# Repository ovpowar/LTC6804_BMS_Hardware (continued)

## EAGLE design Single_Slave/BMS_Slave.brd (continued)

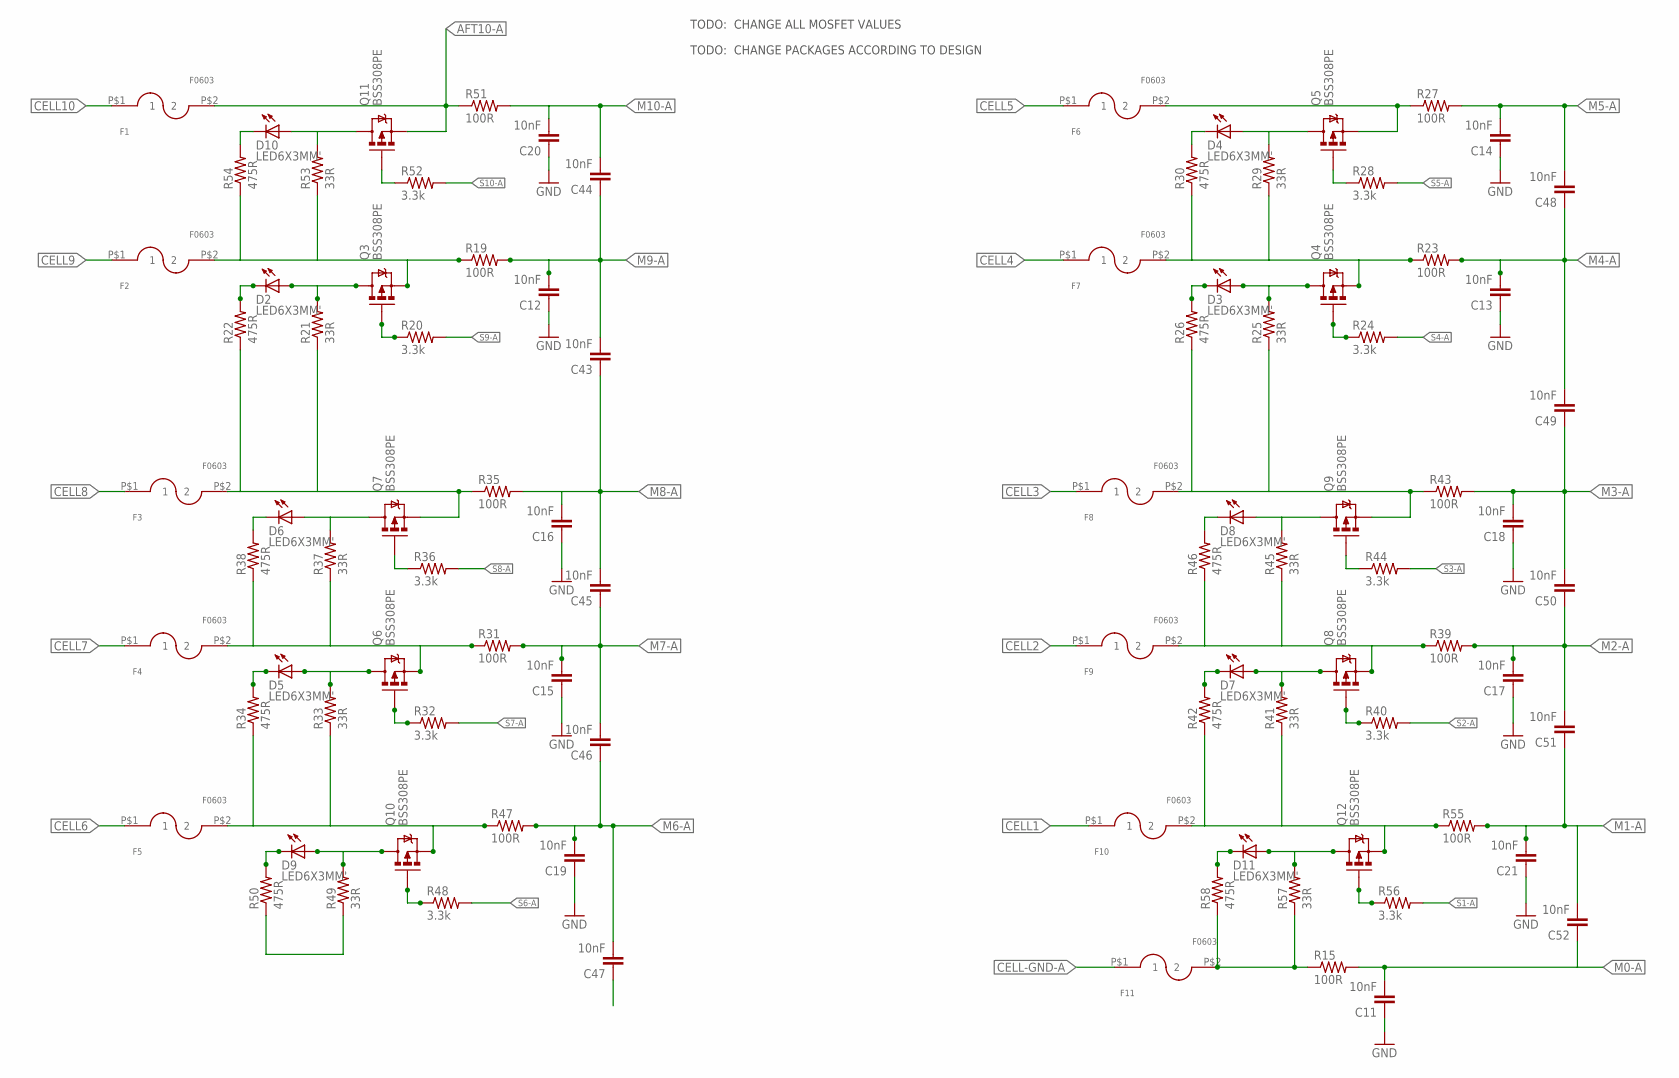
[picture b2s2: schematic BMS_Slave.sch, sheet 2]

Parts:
C11, C12, C13, C14, C15, C16, C17, C18, C19, C20, C21, C43, C44, C45, C46, C47, C48, C49, C50, C51, C52: 10nF; 0603
D2, D3, D4, D5, D6, D7, D8, D9, D10, D11: LED6X3MM'; LED0603
F1, F2, F3, F4, F5, F6, F7, F8, F9, F10, F11: F0603; 0603
Q3, Q4, Q5, Q6, Q7, Q8, Q9, Q10, Q11, Q12: BSS308PE; SOT23-3
R15, R19, R23, R27, R31, R35, R39, R43, R47, R51, R55: 100R; 0603
R20, R24, R28, R32, R36, R40, R44, R48, R52, R56: 3.3k; 0603
R21, R25, R29, R33, R37, R41, R45, R49, R53, R57: 33R; 2512
R22, R26, R30, R34, R38, R42, R46, R50, R54, R58: 475R; 0603

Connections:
AFT0: F11.P$2 (2), R15.P$1 (1), R57.1, R58.P$1 (1)
AFT1: F10.P$2 (2), Q12.2 (S), R41.1, R42.P$1 (1), R55.P$1 (1)
AFT2: F9.P$2 (2), Q8.2 (S), R39.P$1 (1), R45.1, R46.P$1 (1)
AFT3: F8.P$2 (2), Q9.2 (S), R25.1, R26.P$1 (1), R43.P$1 (1)
AFT4: F7.P$2 (2), Q4.2 (S), R23.P$1 (1), R29.1, R30.P$1 (1)
AFT5: F6.P$2 (2), Q5.2 (S), R27.P$1 (1), R49.1, R50.P$1 (1)
AFT6: F5.P$2 (2), Q10.2 (S), R33.1, R34.P$1 (1), R47.P$1 (1)
AFT7: F4.P$2 (2), Q6.2 (S), R31.P$1 (1), R37.1, R38.P$1 (1)
AFT8: F3.P$2 (2), Q7.2 (S), R21.1, R22.P$1 (1), R35.P$1 (1)
AFT9: F2.P$2 (2), Q3.2 (S), R19.P$1 (1), R53.1, R54.P$1 (1)
AFT10-A: F1.P$2 (2), Q11.2 (S), R51.P$1 (1); also elsewhere on the board
CELL1: F10.P$1 (1); also elsewhere on the board
CELL2: F9.P$1 (1); also elsewhere on the board
CELL3: F8.P$1 (1); also elsewhere on the board
CELL4: F7.P$1 (1); also elsewhere on the board
CELL5: F6.P$1 (1); also elsewhere on the board
CELL6: F5.P$1 (1); also elsewhere on the board
CELL7: F4.P$1 (1); also elsewhere on the board
CELL8: F3.P$1 (1); also elsewhere on the board
CELL9: F2.P$1 (1); also elsewhere on the board
CELL10: F1.P$1 (1); also elsewhere on the board
CELL-GND-A: F11.P$1 (1); also elsewhere on the board
GNDA: C11.P$1 (1), C12.P$1 (1), C13.P$1 (1), C14.P$1 (1), C15.P$1 (1), C16.P$1 (1), C17.P$1 (1), C18.P$1 (1), C19.P$1 (1), C20.P$1 (1), C21.P$1 (1); also elsewhere on the board
M0-A: C11.P$2 (2), C52.P$1 (1), R15.P$2 (2); also elsewhere on the board
M1-A: C21.P$2 (2), C51.P$1 (1), C52.P$2 (2), R55.P$2 (2); also elsewhere on the board
M2-A: C17.P$2 (2), C50.P$1 (1), C51.P$2 (2), R39.P$2 (2); also elsewhere on the board
M3-A: C18.P$2 (2), C49.P$1 (1), C50.P$2 (2), R43.P$2 (2); also elsewhere on the board
M4-A: C13.P$2 (2), C48.P$1 (1), C49.P$2 (2), R23.P$2 (2); also elsewhere on the board
M5-A: C14.P$2 (2), C47.P$1 (1), C48.P$2 (2), R27.P$2 (2); also elsewhere on the board
M6-A: C19.P$2 (2), C46.P$1 (1), C47.P$2 (2), R47.P$2 (2); also elsewhere on the board
M7-A: C15.P$2 (2), C45.P$1 (1), C46.P$2 (2), R31.P$2 (2); also elsewhere on the board
M8-A: C16.P$2 (2), C43.P$1 (1), C45.P$2 (2), R35.P$2 (2); also elsewhere on the board
M9-A: C12.P$2 (2), C43.P$2 (2), C44.P$1 (1), R19.P$2 (2); also elsewhere on the board
M10-A: C20.P$2 (2), C44.P$2 (2), R51.P$2 (2); also elsewhere on the board
unnamed: D2.P$1 (A), Q3.3 (D), R21.2
unnamed: D2.P$2 (C), R22.P$2 (2)
unnamed: Q3.1 (G), R20.P$1 (1)
unnamed: D3.P$1 (A), Q4.3 (D), R25.2
unnamed: D3.P$2 (C), R26.P$2 (2)
unnamed: Q4.1 (G), R24.P$1 (1)
unnamed: D4.P$1 (A), Q5.3 (D), R29.2
unnamed: D4.P$2 (C), R30.P$2 (2)
unnamed: Q5.1 (G), R28.P$1 (1)
unnamed: D5.P$1 (A), Q6.3 (D), R33.2
unnamed: D5.P$2 (C), R34.P$2 (2)
unnamed: Q6.1 (G), R32.P$1 (1)
unnamed: D6.P$1 (A), Q7.3 (D), R37.2
unnamed: D6.P$2 (C), R38.P$2 (2)
unnamed: Q7.1 (G), R36.P$1 (1)
unnamed: D7.P$1 (A), Q8.3 (D), R41.2
unnamed: D7.P$2 (C), R42.P$2 (2)
unnamed: Q8.1 (G), R40.P$1 (1)
unnamed: D8.P$1 (A), Q9.3 (D), R45.2
unnamed: D8.P$2 (C), R46.P$2 (2)
unnamed: Q9.1 (G), R44.P$1 (1)
unnamed: D10.P$1 (A), Q11.3 (D), R53.2
unnamed: D10.P$2 (C), R54.P$2 (2)
unnamed: Q11.1 (G), R52.P$1 (1)
unnamed: D9.P$1 (A), Q10.3 (D), R49.2
unnamed: D9.P$2 (C), R50.P$2 (2)
unnamed: Q10.1 (G), R48.P$1 (1)
unnamed: D11.P$1 (A), Q12.3 (D), R57.2
unnamed: D11.P$2 (C), R58.P$2 (2)
unnamed: Q12.1 (G), R56.P$1 (1)
S1-A: R56.P$2 (2); also elsewhere on the board
S2-A: R40.P$2 (2); also elsewhere on the board
S3-A: R44.P$2 (2); also elsewhere on the board
S4-A: R24.P$2 (2); also elsewhere on the board
S5-A: R28.P$2 (2); also elsewhere on the board
S6-A: R48.P$2 (2); also elsewhere on the board
S7-A: R32.P$2 (2); also elsewhere on the board
S8-A: R36.P$2 (2); also elsewhere on the board
S9-A: R20.P$2 (2); also elsewhere on the board
S10-A: R52.P$2 (2); also elsewhere on the board

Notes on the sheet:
TODO: CHANGE ALL MOSFET VALUES
TODO: CHANGE PACKAGES ACCORDING TO DESIGN

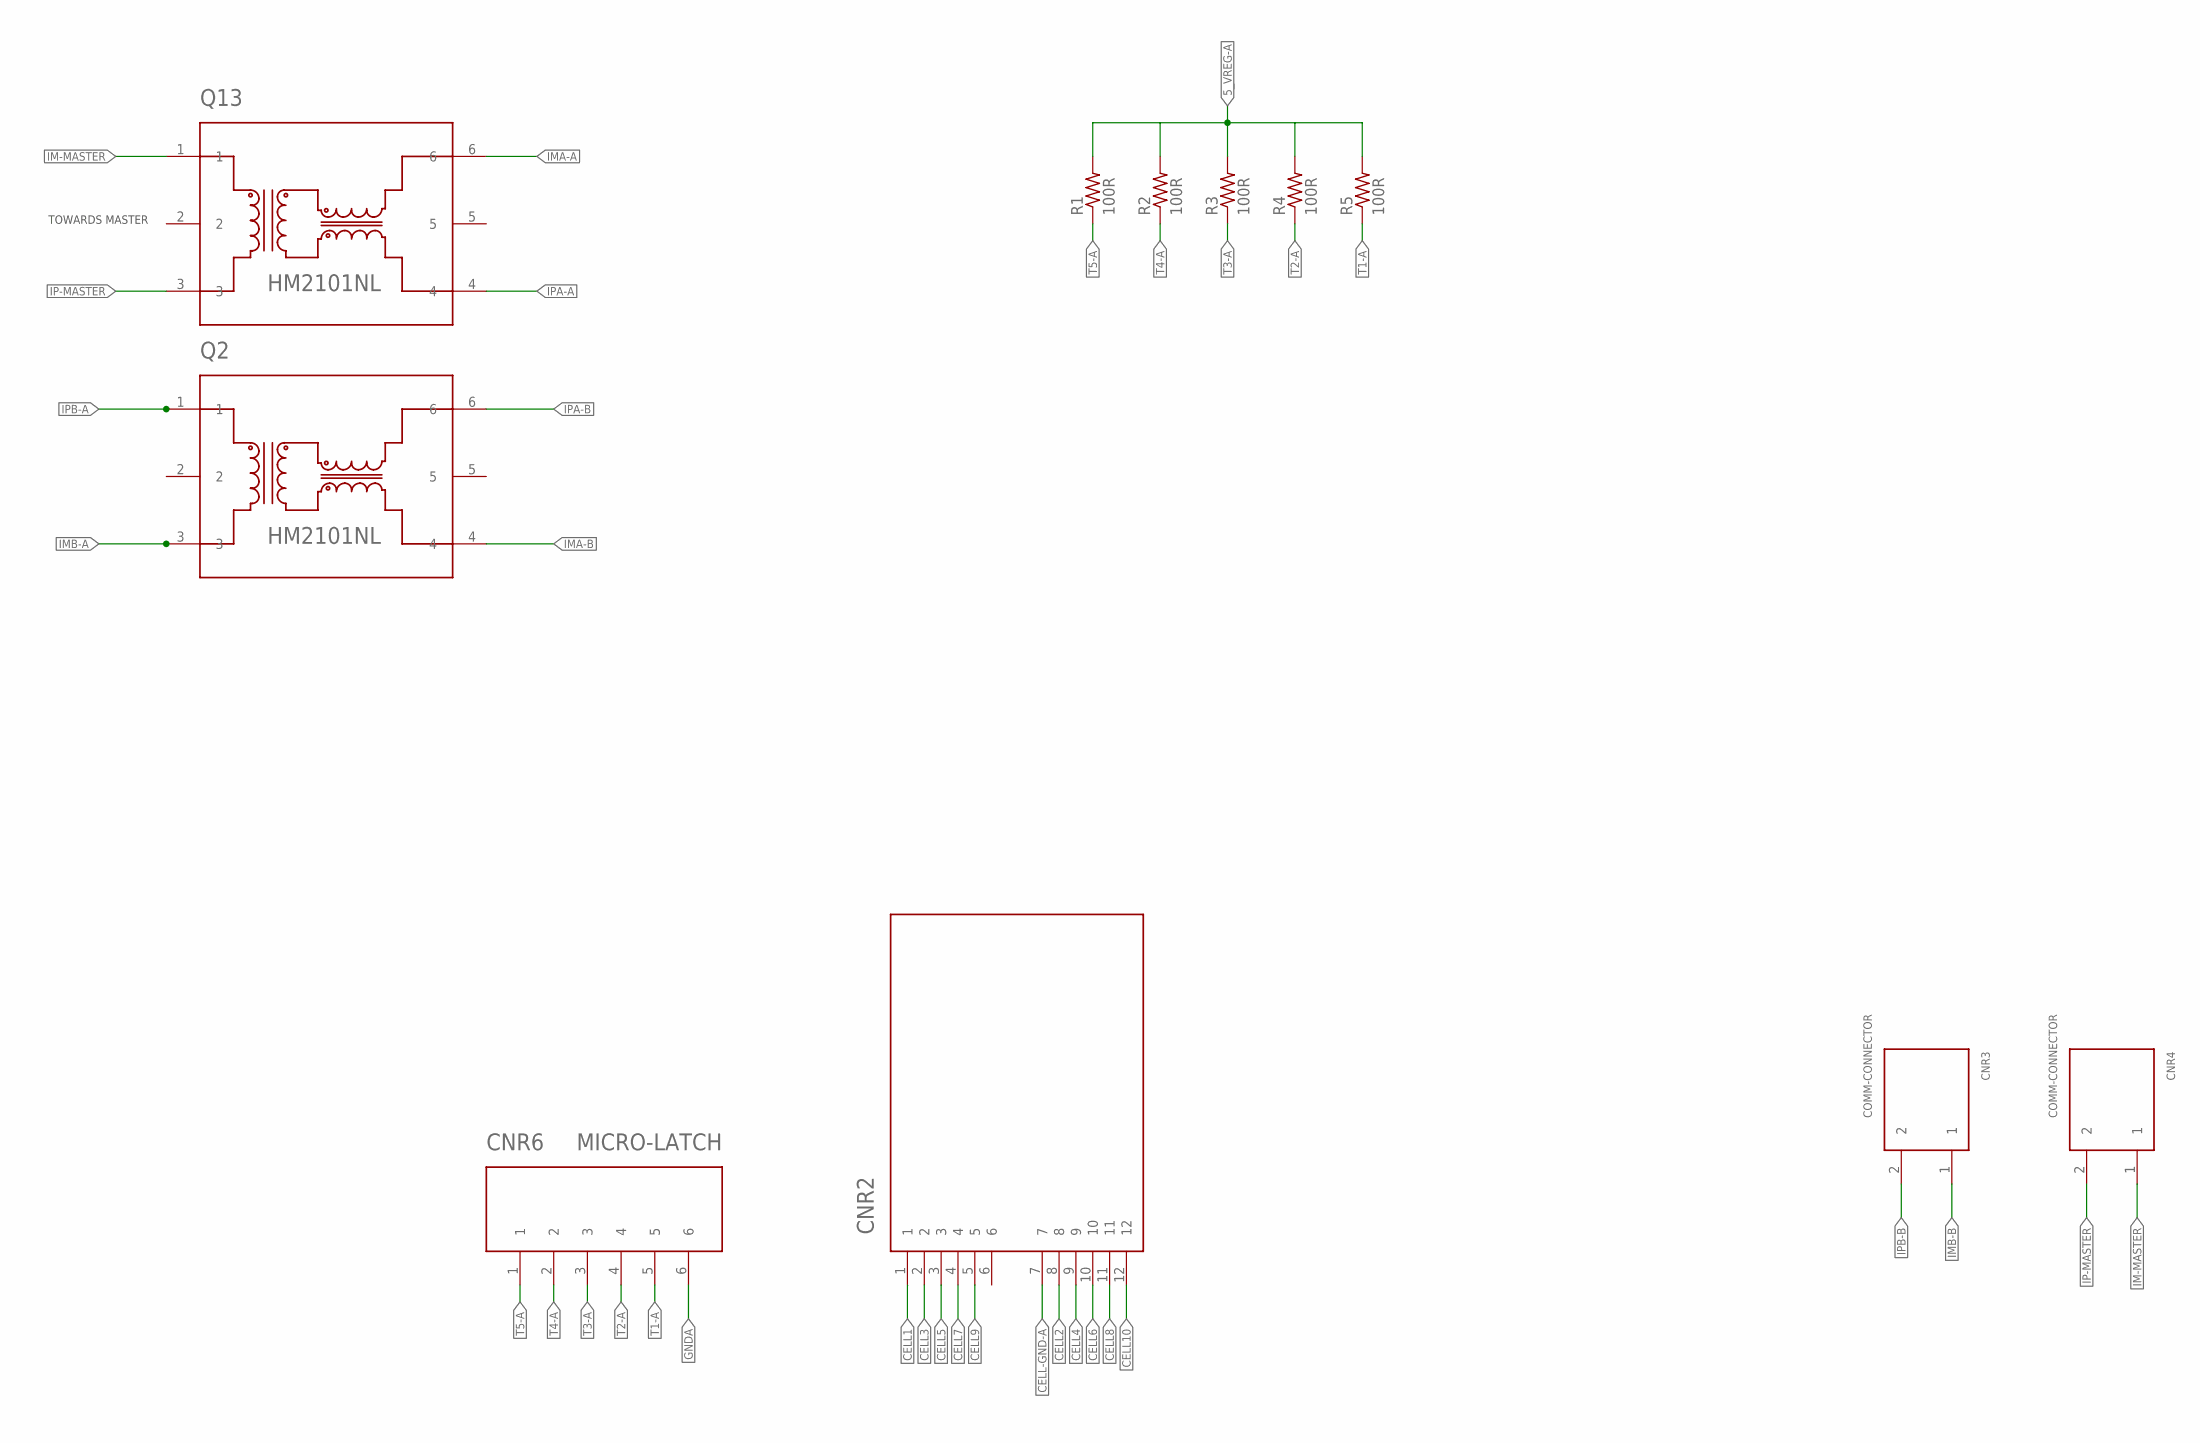
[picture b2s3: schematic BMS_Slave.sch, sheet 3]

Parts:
CNR2: CELL-CONNECTORMOLEX-MICROFIT; 0430451200
CNR3, CNR4: COMM-CONNECTOR; 105313-2202
CNR6: MICRO-LATCH; 0532530670
Q2, Q13: HM2101NL
R1, R2, R3, R4, R5: 100R; 0603

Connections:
5_VREG-A: R1.P$2 (2), R2.P$2 (2), R3.P$2 (2), R4.P$2 (2), R5.P$2 (2); also elsewhere on the board
CELL1: CNR2.1; also elsewhere on the board
CELL2: CNR2.8; also elsewhere on the board
CELL3: CNR2.2; also elsewhere on the board
CELL4: CNR2.9; also elsewhere on the board
CELL5: CNR2.3; also elsewhere on the board
CELL6: CNR2.10; also elsewhere on the board
CELL7: CNR2.4; also elsewhere on the board
CELL8: CNR2.11; also elsewhere on the board
CELL9: CNR2.5; also elsewhere on the board
CELL10: CNR2.12; also elsewhere on the board
CELL-GND-A: CNR2.7; also elsewhere on the board
GNDA: CNR6.6; also elsewhere on the board
IM-MASTER: CNR4.1, Q13.1
IMA-A: Q13.6; also elsewhere on the board
IMA-B: Q2.4
IMB-A: Q2.3; also elsewhere on the board
IMB-B: CNR3.1
IP-MASTER: CNR4.2, Q13.3
IPA-A: Q13.4; also elsewhere on the board
IPA-B: Q2.6
IPB-A: Q2.1; also elsewhere on the board
IPB-B: CNR3.2
T1-A: CNR6.5, R5.P$1 (1); also elsewhere on the board
T2-A: CNR6.4, R4.P$1 (1); also elsewhere on the board
T3-A: CNR6.3, R3.P$1 (1); also elsewhere on the board
T4-A: CNR6.2, R2.P$1 (1); also elsewhere on the board
T5-A: CNR6.1, R1.P$1 (1); also elsewhere on the board

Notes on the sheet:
TOWARDS MASTER

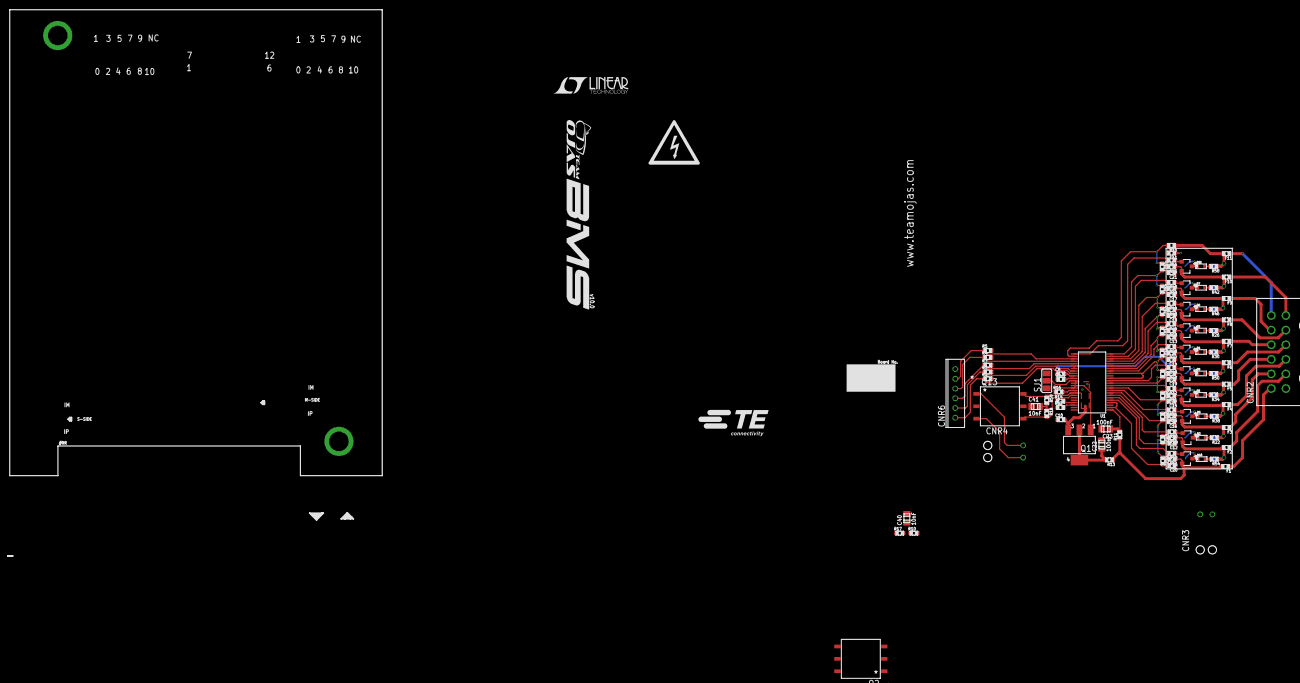
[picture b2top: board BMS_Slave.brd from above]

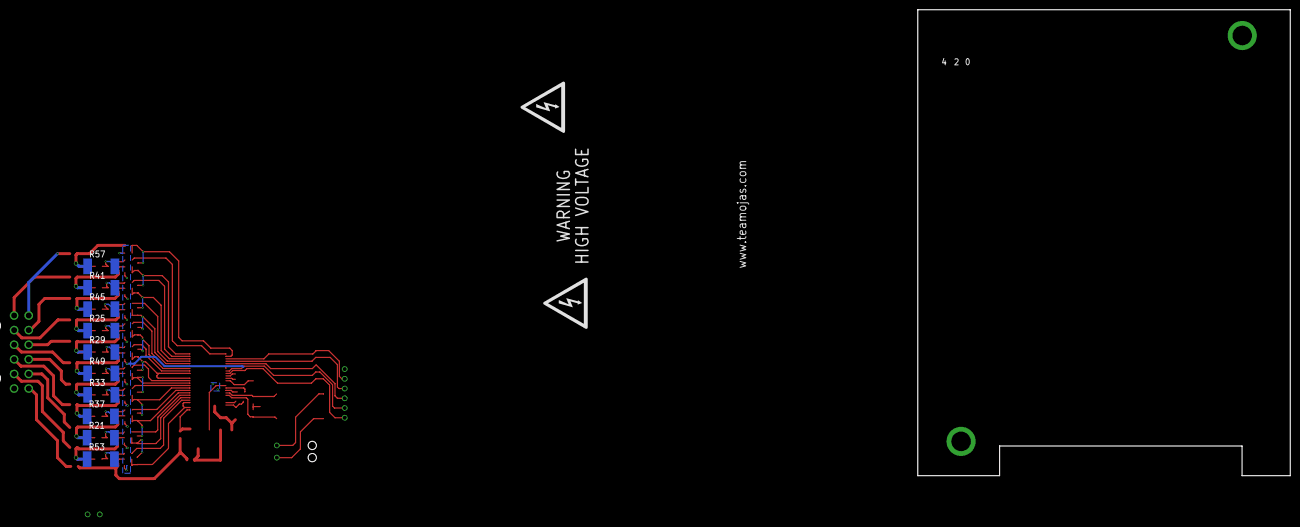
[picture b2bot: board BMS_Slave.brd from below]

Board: 2 copper layers, 76.5 x 95.7 mm, 123 parts (10 on the bottom side), 97 nets.

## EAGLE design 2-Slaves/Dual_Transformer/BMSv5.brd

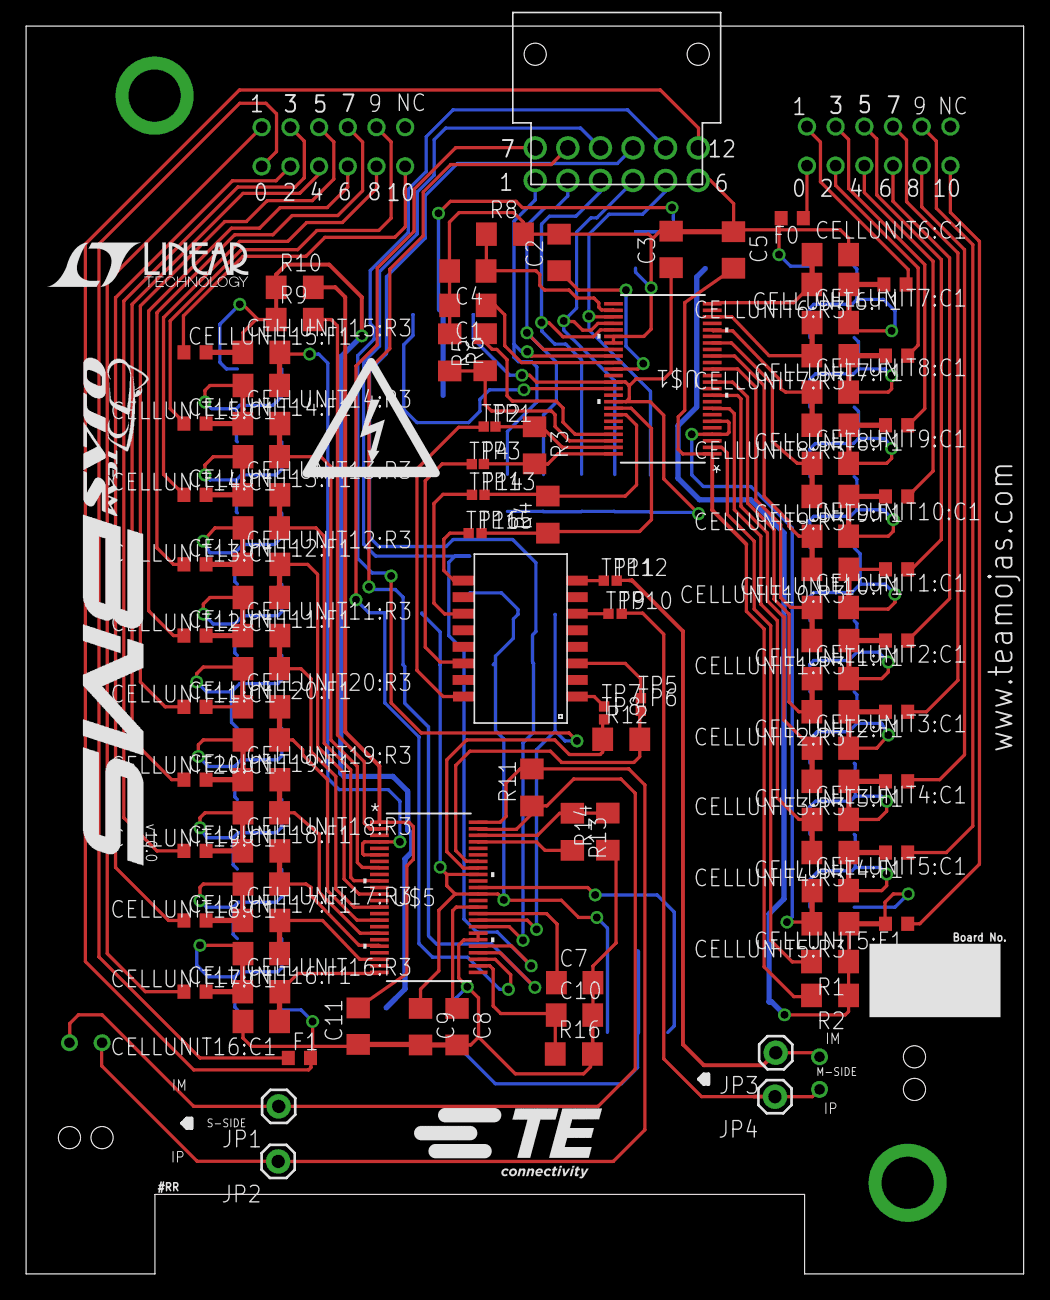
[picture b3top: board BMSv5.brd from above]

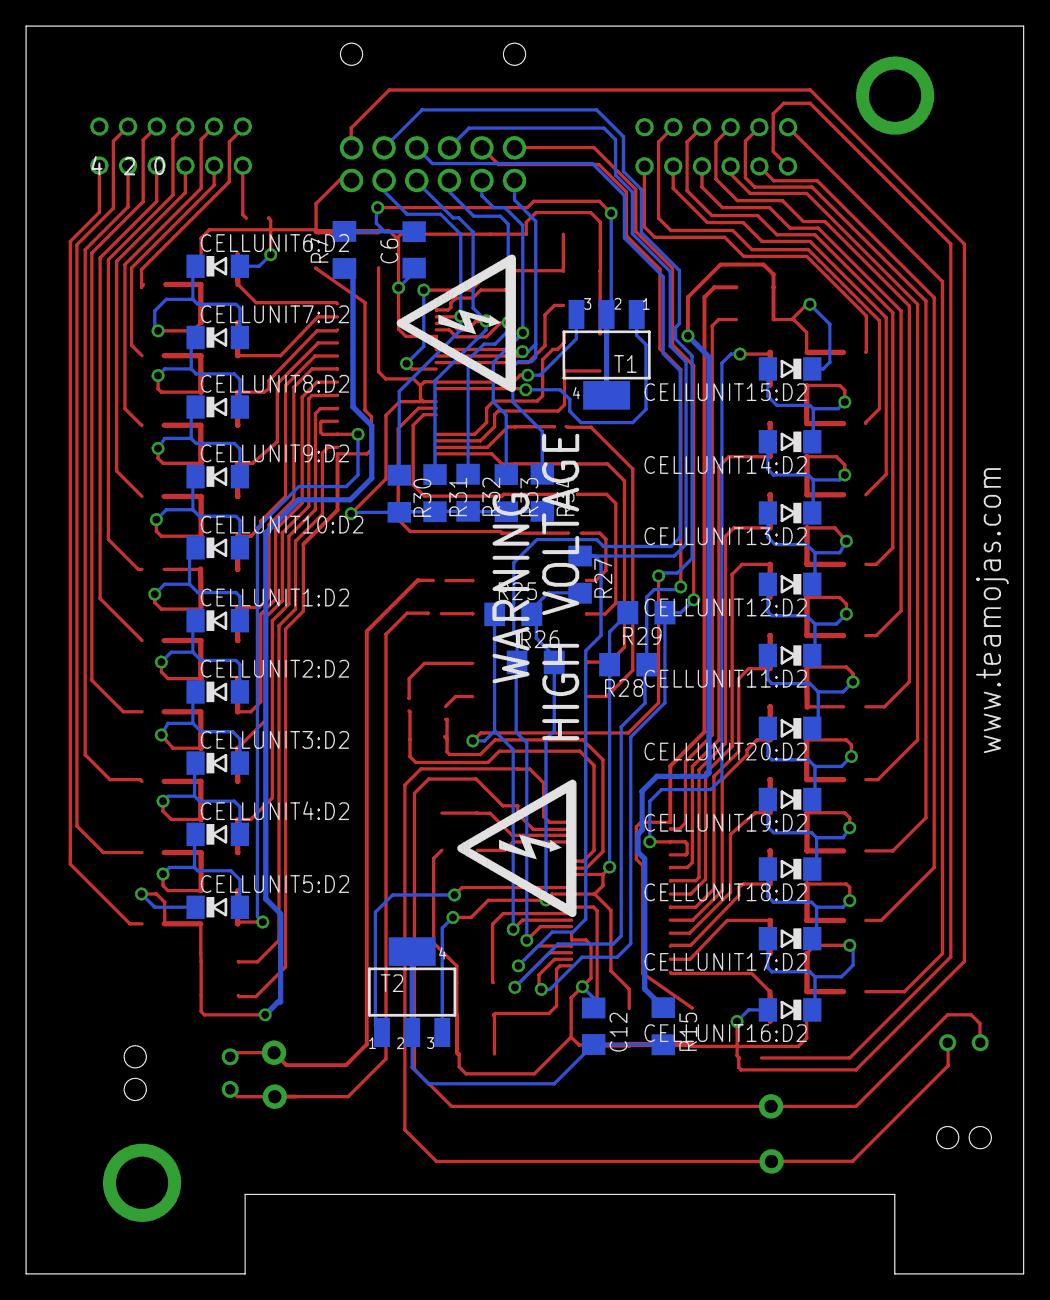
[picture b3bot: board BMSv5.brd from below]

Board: 2 copper layers, 76.5 x 95.7 mm, 150 parts (36 on the bottom side), 112 nets.

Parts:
C1, C2, C3, C7, C8, C9: 1uf; C1206
C4, C10: 10nf; C1206
C5, C6, C11, C12: 100nf; C1206
CELLUNIT1:C1, CELLUNIT2:C1, CELLUNIT3:C1, CELLUNIT4:C1, CELLUNIT5:C1, CELLUNIT6:C1, CELLUNIT7:C1, CELLUNIT8:C1, CELLUNIT9:C1, CELLUNIT10:C1, CELLUNIT11:C1, CELLUNIT12:C1, CELLUNIT13:C1, CELLUNIT14:C1, CELLUNIT15:C1, CELLUNIT16:C1, CELLUNIT17:C1, CELLUNIT18:C1, CELLUNIT19:C1, CELLUNIT20:C1: C1206
CELLUNIT1:D2, CELLUNIT2:D2, CELLUNIT3:D2, CELLUNIT4:D2, CELLUNIT5:D2, CELLUNIT6:D2, CELLUNIT7:D2, CELLUNIT8:D2, CELLUNIT9:D2, CELLUNIT10:D2, CELLUNIT11:D2, CELLUNIT12:D2, CELLUNIT13:D2, CELLUNIT14:D2, CELLUNIT15:D2, CELLUNIT16:D2, CELLUNIT17:D2, CELLUNIT18:D2, CELLUNIT19:D2, CELLUNIT20:D2: SOD80C
CELLUNIT1:F1, CELLUNIT2:F1, CELLUNIT3:F1, CELLUNIT4:F1, CELLUNIT5:F1, CELLUNIT6:F1, CELLUNIT7:F1, CELLUNIT8:F1, CELLUNIT9:F1, CELLUNIT10:F1, CELLUNIT11:F1, CELLUNIT12:F1, CELLUNIT13:F1, CELLUNIT14:F1, CELLUNIT15:F1, CELLUNIT16:F1, CELLUNIT17:F1, CELLUNIT18:F1, CELLUNIT19:F1, CELLUNIT20:F1: R0603
CELLUNIT1:R3, CELLUNIT2:R3, CELLUNIT3:R3, CELLUNIT4:R3, CELLUNIT5:R3, CELLUNIT6:R3, CELLUNIT7:R3, CELLUNIT8:R3, CELLUNIT9:R3, CELLUNIT10:R3, CELLUNIT11:R3, CELLUNIT12:R3, CELLUNIT13:R3, CELLUNIT14:R3, CELLUNIT15:R3, CELLUNIT16:R3, CELLUNIT17:R3, CELLUNIT18:R3, CELLUNIT19:R3, CELLUNIT20:R3: R1206
F0, F1: R0603
JP1, JP2, JP3, JP4: 1X01
R1, R2, R7, R8, R9, R10, R15, R16: 100; R1206
R3, R4, R11, R12: 120; R1206
R5, R13: 806; R1206
R6, R14: 1.2k; R1206
R25, R26, R27, R28, R29, R30, R31, R32, R33, R34: R1206
T1, T2: SOT223
TP1, TP2, TP3, TP4, TP5, TP6, TP7, TP8, TP9, TP10, TP11, TP12, TP13, TP14, TP15, TP16: TPTP08SQ; TP08SQ
U$1, U$5: LTC6804; SSOP-48_FW
U$2: HX1188N; HX1188
U$3, U$7: TE12PIN
U$4, U$6: MOLEX_2_PIN; MOLEX_2PIN
U$8: MOLEX_12_PIN; MOLEX_12PIN

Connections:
5V: C3.1, R30.2, R31.2, R32.2, R33.2, R34.2, T1.3, U$1.37, U$1.40
5VREG1: C9.1, R25.2, R26.2, R27.2, R28.2, R29.2, T2.3, U$5.37, U$5.40
AFTFUSE: CELLUNIT5:D2.C, CELLUNIT5:F1.2, CELLUNIT5:R3.1, R1.1, R2.1, R7.1
AFTFUSE1: CELLUNIT15:D2.C, CELLUNIT15:F1.2, CELLUNIT15:R3.1, R9.1, R10.1, R15.1
B1: CELLUNIT6:F1.1, U$3.2
B2: CELLUNIT7:F1.1, U$3.3
B3: CELLUNIT8:F1.1, U$3.4
B4: CELLUNIT9:F1.1, U$3.5
B5: CELLUNIT10:F1.1, U$3.6
B6: CELLUNIT1:F1.1, U$3.7
B7: CELLUNIT2:F1.1, U$3.8
B8: CELLUNIT3:F1.1, U$3.9
B9: CELLUNIT4:F1.1, U$3.10
B10: CELLUNIT5:F1.1, U$3.11
B11: CELLUNIT16:F1.1, U$7.2
B12: CELLUNIT17:F1.1, U$7.3
B13: CELLUNIT18:F1.1, U$7.4
B14: CELLUNIT19:F1.1, U$7.5
B15: CELLUNIT20:F1.1, U$7.6
B16: CELLUNIT11:F1.1, U$7.7
B17: CELLUNIT12:F1.1, U$7.8
B18: CELLUNIT13:F1.1, U$7.9
B19: CELLUNIT14:F1.1, U$7.10
B20: CELLUNIT15:F1.1, U$7.11
C0: C4.1, R8.1, U$1.26
C0A: C10.1, R16.1, U$5.26
C1: CELLUNIT6:C1.1, CELLUNIT6:R3.2, U$1.24
C1A: CELLUNIT16:C1.1, CELLUNIT16:R3.2, U$5.24
C2: CELLUNIT7:C1.1, CELLUNIT7:R3.2, U$1.22
C2A: CELLUNIT17:C1.1, CELLUNIT17:R3.2, U$5.22
C3: CELLUNIT8:C1.1, CELLUNIT8:R3.2, U$1.20
C3A: CELLUNIT18:C1.1, CELLUNIT18:R3.2, U$5.20
C4: CELLUNIT9:C1.1, CELLUNIT9:R3.2, U$1.18
C4A: CELLUNIT19:C1.1, CELLUNIT19:R3.2, U$5.18
C5: CELLUNIT10:C1.1, CELLUNIT10:R3.2, U$1.16
C5A: CELLUNIT20:C1.1, CELLUNIT20:R3.2, U$5.16
C6: CELLUNIT1:C1.1, CELLUNIT1:R3.2, U$1.14
C6A: CELLUNIT11:C1.1, CELLUNIT11:R3.2, U$5.14
C7: CELLUNIT2:C1.1, CELLUNIT2:R3.2, U$1.12
C7A: CELLUNIT12:C1.1, CELLUNIT12:R3.2, U$5.12
C8: CELLUNIT3:C1.1, CELLUNIT3:R3.2, U$1.10
C8A: CELLUNIT13:C1.1, CELLUNIT13:R3.2, U$5.10
C9: CELLUNIT4:C1.1, CELLUNIT4:R3.2, U$1.8
C9A: CELLUNIT14:C1.1, CELLUNIT14:R3.2, U$5.8
C10: CELLUNIT5:C1.1, CELLUNIT5:R3.2, U$1.4, U$1.6
C10A: CELLUNIT15:C1.1, CELLUNIT15:R3.2, U$5.4, U$5.6
CELL0V: F0.1, U$3.1
CELL0V1A: F1.1, U$7.1
CI1: CELLUNIT11:C1.2, CELLUNIT11:D2.A, CELLUNIT20:D2.C, CELLUNIT20:F1.2, CELLUNIT20:R3.1
CI5: CELLUNIT1:C1.2, CELLUNIT1:D2.A, CELLUNIT10:D2.C, CELLUNIT10:F1.2, CELLUNIT10:R3.1
CONINM: JP3.1, TP12.TP, U$6.P$2
CONINM1: TP11.TP, U$2.8
CONINP: JP4.1, TP10.TP, U$6.P$1
CONINP1: TP9.TP, U$2.6
GND: C1.2, C2.2, C3.2, C4.2, C5.1, C6.1, CELLUNIT6:C1.2, CELLUNIT6:D2.A, F0.2, R6.1, R8.2, U$1.30, U$1.31, U$8.P6
GND1: C7.2, C8.2, C9.2, C10.2, C11.1, C12.1, CELLUNIT16:C1.2, CELLUNIT16:D2.A, F1.2, R14.1, R16.2, U$5.30, U$5.31, U$8.P12
IMA: R4.1, TP15.TP, U$1.41
IMA1: TP7.TP, U$2.1
IMA1O: R12.1, TP8.TP, U$5.41
IMAT: TP16.TP, U$2.9
IMB: TP2.TP, U$2.16
IMB1O: JP1.1, R11.1, U$4.P$1, U$5.47
IMBO: R3.1, TP1.TP, U$1.47
IPA: R4.2, TP13.TP, U$1.42
IPA1: TP5.TP, U$2.3
IPA1O: R12.2, TP6.TP, U$5.42
IPAT: TP14.TP, U$2.11
IPB: TP4.TP, U$2.14
IPB1O: JP2.1, R11.2, U$4.P$2, U$5.48
IPBO: R3.2, TP3.TP, U$1.48
unnamed: C6.2, R7.2, T1.2, T1.4
unnamed: CELLUNIT1:D2.C, CELLUNIT1:F1.2, CELLUNIT1:R3.1, CELLUNIT2:C1.2, CELLUNIT2:D2.A
unnamed: C5.2, R2.2, U$1.1
unnamed: T1.1, U$1.38
unnamed: R9.2, U$5.2
unnamed: C1.1, U$1.34
unnamed: C2.1, U$1.35
unnamed: R5.1, R6.2, U$1.46
unnamed: C11.2, R10.2, U$5.1
unnamed: R1.2, U$1.2
unnamed: R5.2, U$1.45
unnamed: C7.1, U$5.34
unnamed: C8.1, U$5.35
unnamed: R13.1, R14.2, U$5.46
unnamed: R13.2, U$5.45
unnamed: C12.2, R15.2, T2.2, T2.4
unnamed: CELLUNIT2:D2.C, CELLUNIT2:F1.2, CELLUNIT2:R3.1, CELLUNIT3:C1.2, CELLUNIT3:D2.A
unnamed: CELLUNIT4:D2.C, CELLUNIT4:F1.2, CELLUNIT4:R3.1, CELLUNIT5:C1.2, CELLUNIT5:D2.A
unnamed: CELLUNIT3:D2.C, CELLUNIT3:F1.2, CELLUNIT3:R3.1, CELLUNIT4:C1.2, CELLUNIT4:D2.A
unnamed: T2.1, U$5.38
unnamed: CELLUNIT6:D2.C, CELLUNIT6:F1.2, CELLUNIT6:R3.1, CELLUNIT7:C1.2, CELLUNIT7:D2.A
unnamed: CELLUNIT7:D2.C, CELLUNIT7:F1.2, CELLUNIT7:R3.1, CELLUNIT8:C1.2, CELLUNIT8:D2.A
unnamed: CELLUNIT9:D2.C, CELLUNIT9:F1.2, CELLUNIT9:R3.1, CELLUNIT10:C1.2, CELLUNIT10:D2.A
unnamed: CELLUNIT8:D2.C, CELLUNIT8:F1.2, CELLUNIT8:R3.1, CELLUNIT9:C1.2, CELLUNIT9:D2.A
unnamed: CELLUNIT11:D2.C, CELLUNIT11:F1.2, CELLUNIT11:R3.1, CELLUNIT12:C1.2, CELLUNIT12:D2.A
unnamed: CELLUNIT12:D2.C, CELLUNIT12:F1.2, CELLUNIT12:R3.1, CELLUNIT13:C1.2, CELLUNIT13:D2.A
unnamed: CELLUNIT14:D2.C, CELLUNIT14:F1.2, CELLUNIT14:R3.1, CELLUNIT15:C1.2, CELLUNIT15:D2.A
unnamed: CELLUNIT13:D2.C, CELLUNIT13:F1.2, CELLUNIT13:R3.1, CELLUNIT14:C1.2, CELLUNIT14:D2.A
unnamed: CELLUNIT16:D2.C, CELLUNIT16:F1.2, CELLUNIT16:R3.1, CELLUNIT17:C1.2, CELLUNIT17:D2.A
unnamed: CELLUNIT17:D2.C, CELLUNIT17:F1.2, CELLUNIT17:R3.1, CELLUNIT18:C1.2, CELLUNIT18:D2.A
unnamed: CELLUNIT19:D2.C, CELLUNIT19:F1.2, CELLUNIT19:R3.1, CELLUNIT20:C1.2, CELLUNIT20:D2.A
unnamed: CELLUNIT18:D2.C, CELLUNIT18:F1.2, CELLUNIT18:R3.1, CELLUNIT19:C1.2, CELLUNIT19:D2.A
T1: R30.1, U$1.27, U$8.P5
T2: R31.1, U$1.28, U$8.P4
T3: R32.1, U$1.29, U$8.P3
T4: R33.1, U$1.32, U$8.P2
T5: R34.1, U$1.33, U$8.P1
T11: R29.1, U$5.27, U$8.P7
T12: R28.1, U$5.28, U$8.P8
T13: R27.1, U$5.29, U$8.P9
T14: R26.1, U$5.32, U$8.P10
T15: R25.1, U$5.33, U$8.P11

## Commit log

2018-10-24 Adding Original Files
    - Commiting the original BMS designed 2 years back (No balancing)
    - New design with Balancing
    - Maintained size of PCB
2018-11-08 Single Slave Addition
    - Added Single IC Slave PCBs
2018-11-08 Original BMS Master
    - Added Original Atmega 2560 BMS Master
